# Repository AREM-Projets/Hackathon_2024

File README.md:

# Hackathon_2024
Dépôt pour le projet Hackathon 2024

## Robots sumo
Le code pour les robots sumo est dans la branche *Telecommande_UART*

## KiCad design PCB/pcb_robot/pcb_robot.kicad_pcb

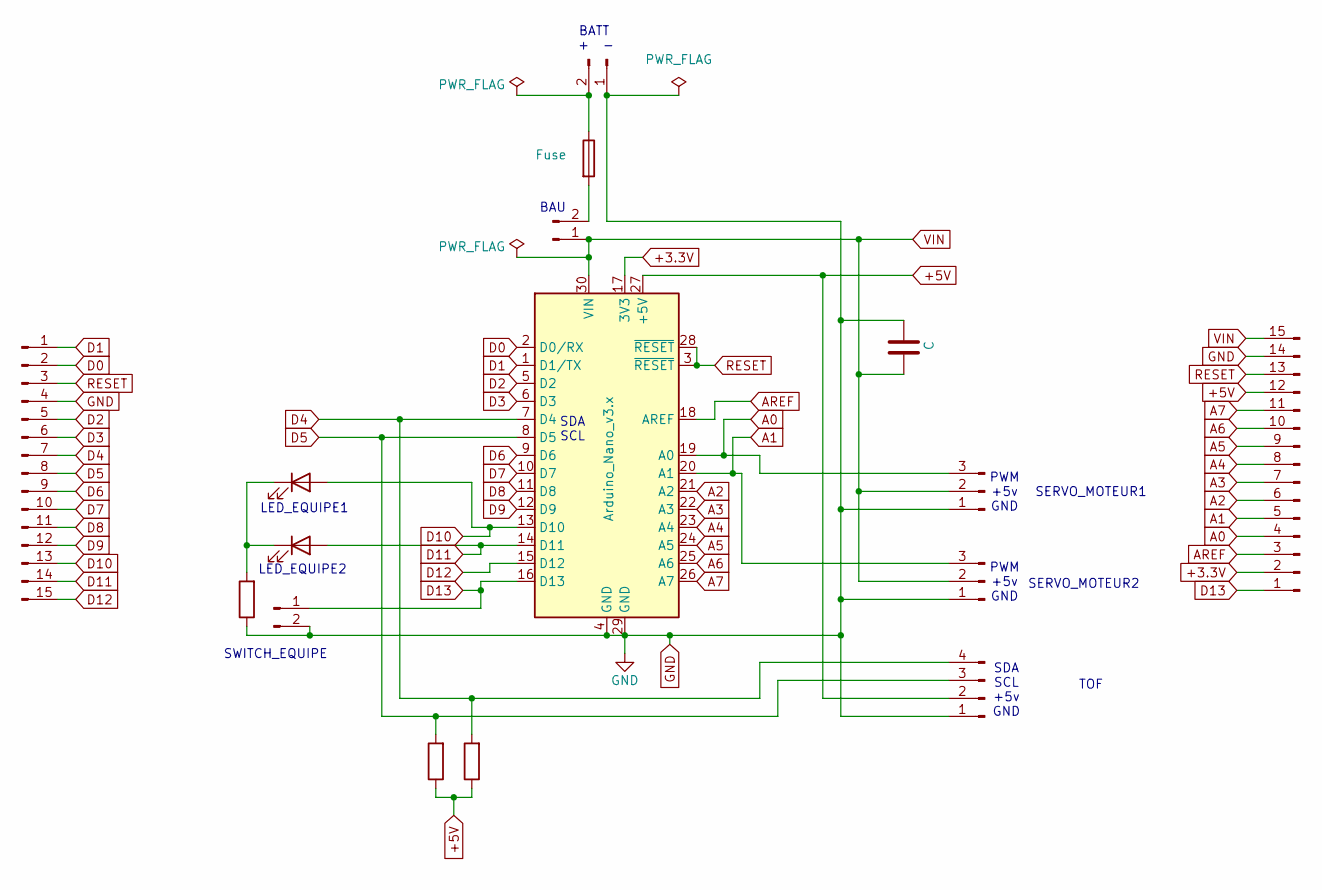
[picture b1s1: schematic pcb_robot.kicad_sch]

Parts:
A1: Arduino_Nano_v3.x; Arduino_Nano
C1: C; C_Elec_6.3x7.7
D1, D2: LED; LED_D3.0mm
F1: Fuse; R_Axial_DIN0309_L9.0mm_D3.2mm_P12.70mm_Horizontal
J2, J3: Conn_01x03_Pin; PinHeader_1x03_P2.54mm_Horizontal
J4, J6: Conn_01x02_Pin; PinHeader_1x02_P2.54mm_Horizontal
J5: Conn_01x02_Pin; JST_EH_B2B-EH-A_1x02_P2.50mm_Vertical
J7: Conn_01x04_Pin; PinHeader_1x04_P2.54mm_Horizontal
J9, J10: Conn_01x15_Pin; PinHeader_1x15_P2.54mm_Vertical
R1, R2, R3: R; R_0805_2012Metric_Pad1.20x1.40mm_HandSolder

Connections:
+3.3V: A1.17 (3V3), J9.2
+5V: A1.27 (+5V), J7.2, J9.12, R2.1, R3.1
A0: A1.19 (A0), J2.3, J9.4
A1: A1.20 (A1), J3.3, J9.5
A2: A1.21 (A2), J9.6
A3: A1.22 (A3), J9.7
A4: A1.23 (A4), J9.8
A5: A1.24 (A5), J9.9
A6: A1.25 (A6), J9.10
A7: A1.26 (A7), J9.11
AREF: A1.18 (AREF), J9.3
D0: A1.2 (D0/RX), J10.2
D1: A1.1 (D1/TX), J10.1
D2: A1.5 (D2), J10.5
D3: A1.6 (D3), J10.6
D4: A1.7 (D4), J7.4, J10.7, R3.2
D5: A1.8 (D5), J7.3, J10.8, R2.2
D6: A1.9 (D6), J10.9
D7: A1.10 (D7), J10.10
D8: A1.11 (D8), J10.11
D9: A1.12 (D9), J10.12
D10: A1.13 (D10), D1.2 (A), J10.13
D11: A1.14 (D11), D2.2 (A), J10.14
D12: A1.15 (D12), J10.15
D13: A1.16 (D13), J6.1, J9.1
GND: A1.4 (GND), A1.29 (GND), C1.2, J2.1, J3.1, J5.1, J6.2, J7.1, J9.14, J10.4, R1.1
unnamed: D1.1 (K), D2.1 (K), R1.2
unnamed: F1.2, J4.2
unnamed: F1.1, J5.2
RESET: A1.3 (~RESET), A1.28 (~RESET), J9.13, J10.3
VIN: A1.30 (VIN), C1.1, J2.2, J3.2, J4.1, J9.15

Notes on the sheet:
SDA SCL +5v GND
SERVO_MOTEUR2
LED_EQUIPE2
BAU
LED_EQUIPE1
SERVO_MOTEUR1
SDA SCL
SWITCH_EQUIPE
+ -
PWM +5v GND
BATT
TOF

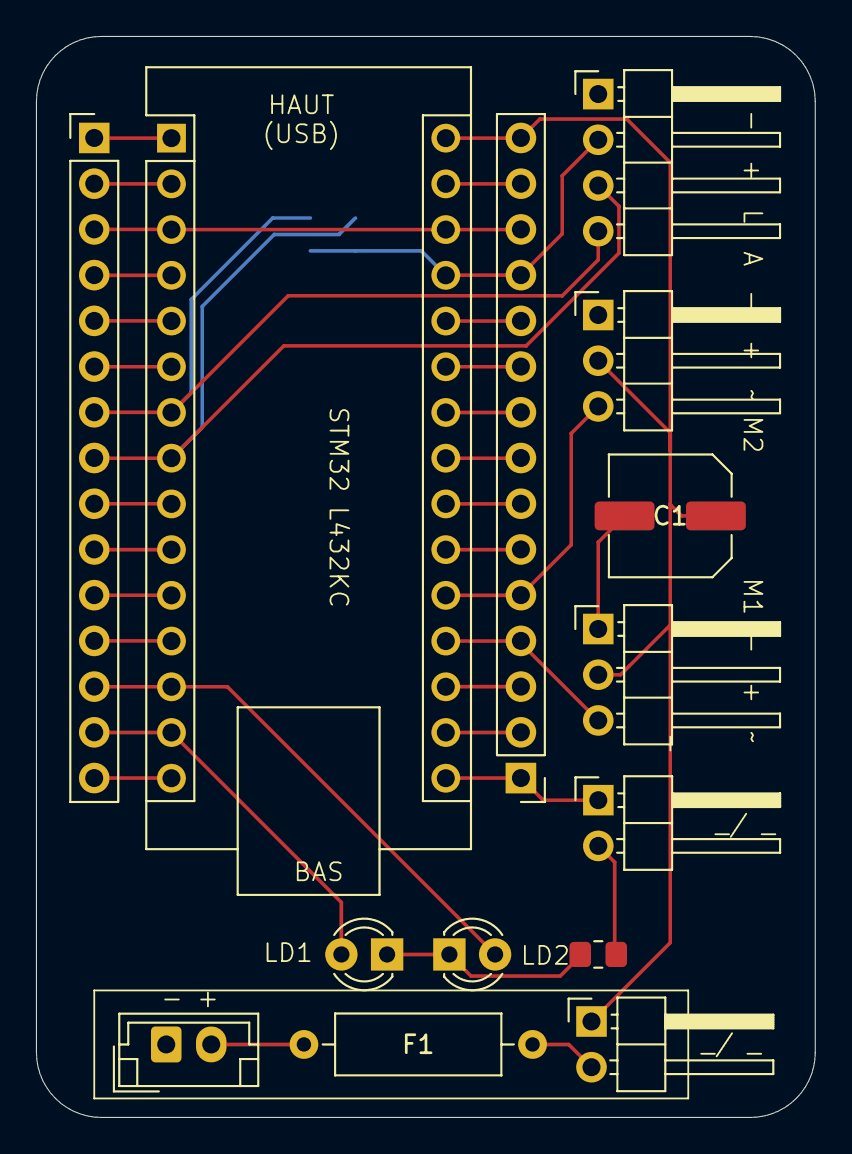
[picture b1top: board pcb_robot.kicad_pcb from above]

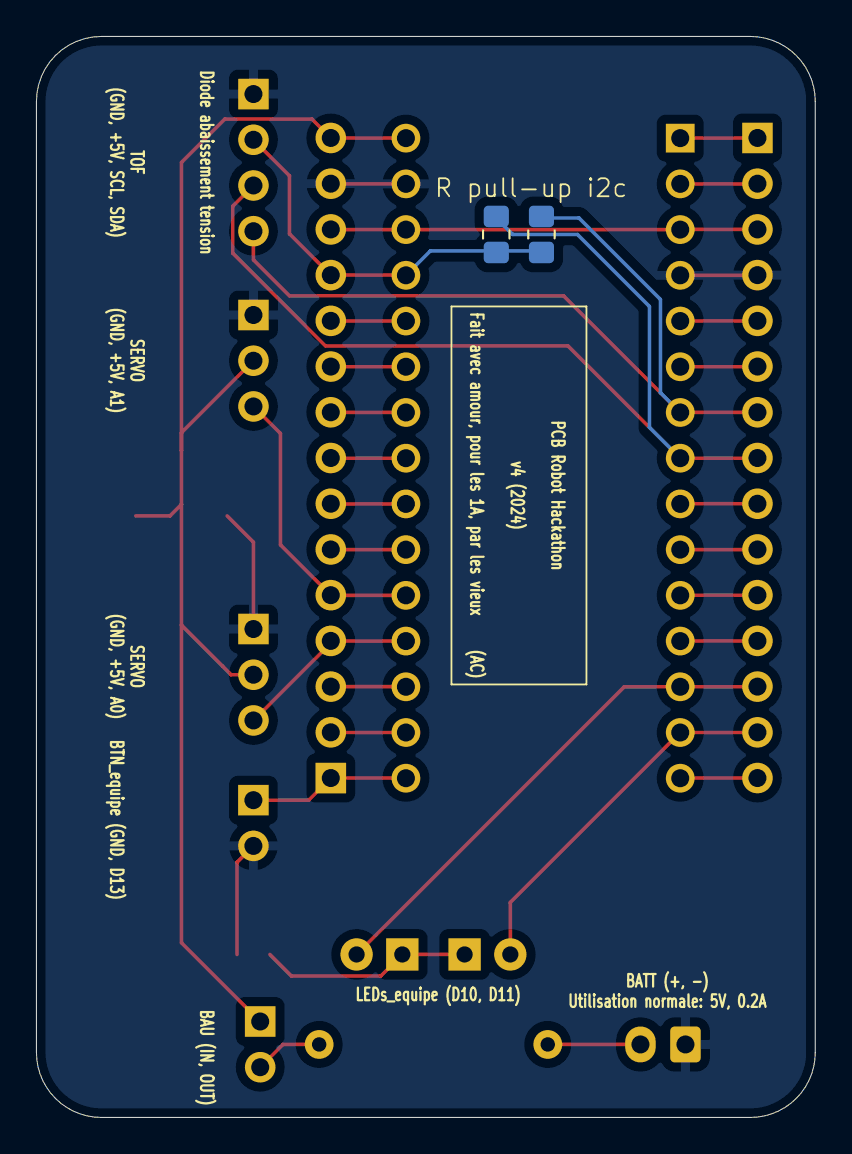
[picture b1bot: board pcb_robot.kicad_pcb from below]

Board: 2 copper layers, 43.3 x 60.1 mm, 16 parts (2 on the bottom side), 31 nets.

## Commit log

2024-09-06 Commit initial
2024-09-06 Ajout README
2024-09-06 Update code fonctionnel roulage 1
2024-09-06 update pins servos et fonctionnement tof. Update pcb pour les bons pins
2024-09-06 update pins avec tof (test fait)
2024-09-06 commentaire
2024-09-07 code ok 1
2024-09-08 update pcb (fuse + rerooting)
2024-09-12 v2 du chassis et update pcb (resistance et retrait servo tete)
2024-09-13 Ajout Regles + Points
2024-09-13 update pcb
2024-09-13 correction empruntes pcb et rerooting
2024-09-13 ajout support 3d tof
2024-09-15 version robot roulage droit avec write millis
2024-09-15 version 1 classes moteur et robot
2024-09-16 classe tof et code roulage et arret proximite ok
2024-09-16 ajout fonction affichage parametres du robot
2024-09-16 fonctions de déplacement absolues ok, revoir pour qu'elles ne soient plus bloquantes...
2024-09-16 tableur de commandes moteur
2024-09-16 ajout trous toit et boutons sur chassis, creation toit
2024-09-16 ajout trous leds sur toit
2024-09-17 odometrie v1
2024-09-17 odometrie ok
2024-09-18 changement noms methodes et deplacement init serial
2024-09-18 reduction marges chassis:rails_plaques, toit:excroissances_fixation
2024-09-18 modifs toit (reduction marge hauteur)
2024-09-18 update pcb (ajout headers pins) + ajustement trou usb chassis 3d
2024-09-18 découpage en modules (avec code commenté dans le main)
2024-09-18 code modules propre
2024-09-18 tracé fichiers impression pcb
2024-09-19 modif code demo
2024-09-19 ajout capa sur pcb et revue chassis (position trous et ajout modele pcb)
2024-09-21 roues évidées
2024-09-22 tracé fichiers pcb final
2024-09-22 update code test
2024-09-23 modifs toit
2024-09-23 ajout de quelques commentaires
2024-09-24 ajout résistances pullup verso pcb
2024-09-24 pcb ajouts
2024-09-24 code pour tester moteurs
2024-09-28 update empruntes cms et modele 3d
2024-10-01 parechoc v1
2024-10-01 ajout fonctions getpos (x, y, angle) plus fonction surcharge stop()
2024-10-03 code FDS v1
2024-10-04 simplification code test moteurs
2024-10-05 changement arborescence projet (tri en libs)
2024-10-05 include
2024-10-10 formation robotique (ajout d'images)
2024-10-10 ajout pare choc et bloc pcb
2024-10-11 creation fichier impression robot entier
2024-10-12 modifs roue (adaptation aux equerres nouveaux moteurs)
2024-10-12 test hard leds equipe et bouton
2024-10-15 changement trous switchs
2024-10-21 corrections pour le merge avec driver
2024-10-21 correction pour le merge
2024-10-21 retrait pcb obsolete
2024-10-22 rien
2024-10-22 correctifs pre_hackathon
2024-10-28 updates suite au prehackathon
2024-10-28 ajout pdf schematics
2024-10-31 mise a jour pour merge avec main (ensemble des fichiers a jour)
2024-10-31 mise a jour avec les bons fichiers pour le merge de driver
2024-11-01 premiere version du README detaille
2024-11-01 ajout tutoriel pdf installation VSCode et PlatformIO plus compilation
2024-11-04 modifs sur fonction TOF et melioration odometrie
2024-11-05 début refactor
2024-11-05 finalisation
2024-11-05 feur
2024-11-06 version finale hackathon 2024
2024-11-06 Ajout remerciements
2024-11-07 finalisation peut être
2024-11-08 test debug
2024-11-09 ajout millis() dans les fcts autorisées
2024-11-09 correction + README
2024-11-09 fix runDistance
2024-11-09 fix runDistance 2
2024-11-22 update avec les derniers fichiers de hackathon_2024
2025-01-09 Ajout traitement commande uart
2025-01-09 Code telecommande uart operationnel
2025-01-23 update controles dynamiques
2025-02-20 Ajout affiches
